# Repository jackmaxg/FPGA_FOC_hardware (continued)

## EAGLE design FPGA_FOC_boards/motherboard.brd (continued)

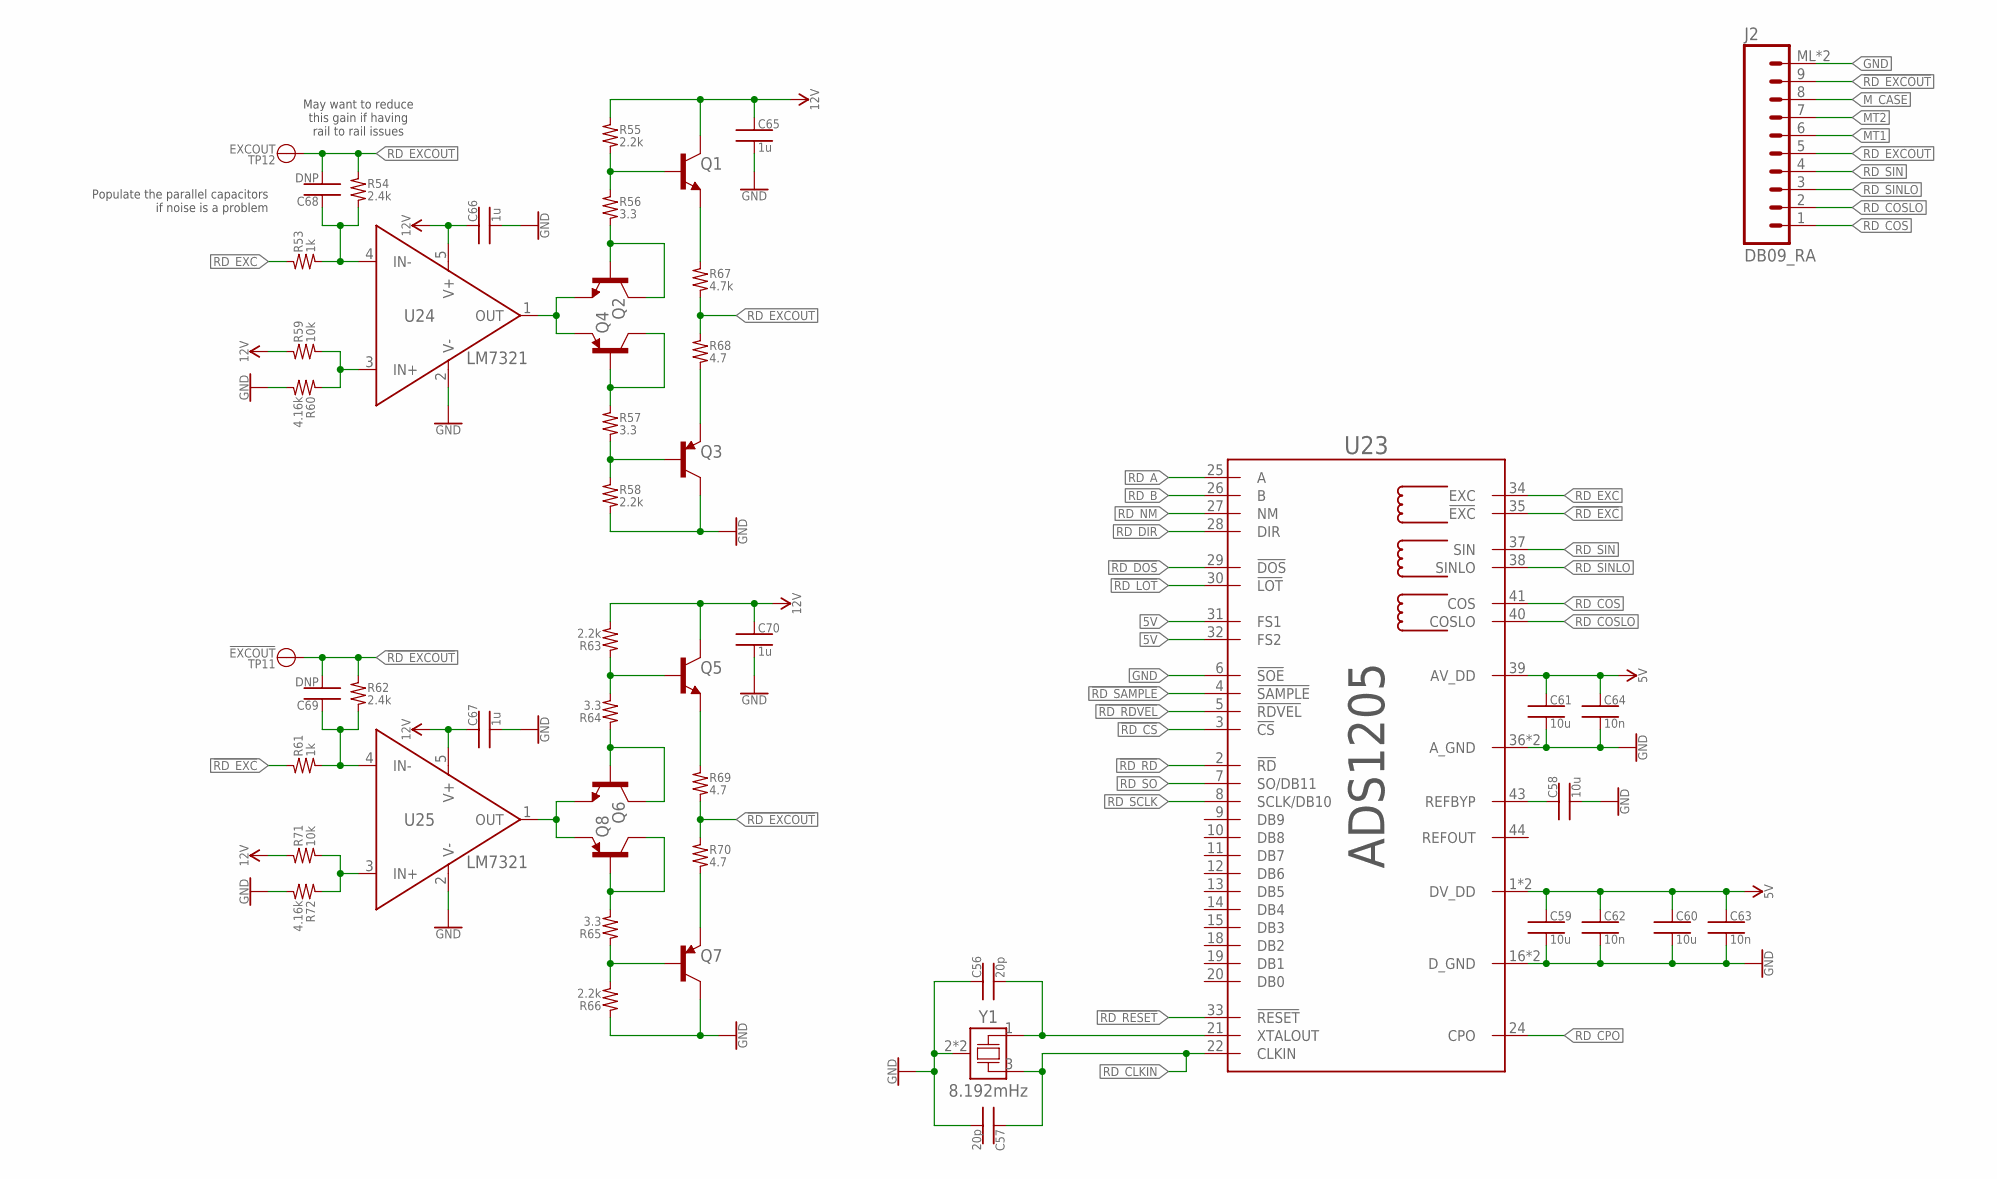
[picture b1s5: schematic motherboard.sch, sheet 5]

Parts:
C56, C57: 20p; 0402
C58, C59, C60, C61: 10u; 0603
C62, C63, C64: 10n; 0402
C65, C66, C67, C70: 1u; 0402
C68, C69: DNP; 0402
J2: DB09_RA; AE10921
Q1, Q2, Q5, Q6: BJT_NPN; SOT23-3
Q3, Q4, Q7, Q8: BJT_PNP; SOT23-3
R53, R61: 1k; 0402
R54, R62: 2.4k; 0402
R55, R58, R63, R66: 2.2k; 0402
R56, R57, R64, R65: 3.3; 0402
R59, R71: 10k; 0402
R60, R72: 4.16k; 0402
R67: 4.7k; 0805
R68, R69, R70: 4.7; 0805
TP11: !EXCOUT; 1X01_50MIL
TP12: EXCOUT; 1X01_50MIL
U23: ADS1205; LQFP44
U24, U25: LM7321; SOT23-5
Y1: 8.192mHz; 5X3.2MM_SMD_XTAL

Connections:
5V: C59.1, C60.1, C61.1, C62.1, C63.1, C64.1, U23.1 (DV_DD), U23.17 (DV_DD), U23.31 (FS1), U23.32 (FS2), U23.39 (AV_DD); also elsewhere on the board
12V: C65.1, C66.1, C67.1, C70.1, Q1.3 (C), Q5.3 (C), R55.1, R59.1, R63.2, R71.1, U24.5 (V+), U25.5 (V+); also elsewhere on the board
!RD_CS: U23.3 (!CS); also elsewhere on the board
!RD_DOS: U23.29 (!DOS); also elsewhere on the board
!RD_EXC: R61.1, U23.35 (!EXC)
!RD_EXCOUT: C69.2, J2.9, R62.1, R69.2, R70.1, TP11.1
!RD_LOT: U23.30 (!LOT); also elsewhere on the board
!RD_RD: U23.2 (!RD); also elsewhere on the board
!RD_RDVEL: U23.5 (!RDVEL); also elsewhere on the board
!RD_RESET: U23.33 (!RESET); also elsewhere on the board
!RD_SAMPLE: U23.4 (!SAMPLE); also elsewhere on the board
GND: C56.1, C57.2, C58.2, C59.2, C60.2, C61.2, C62.2, C63.2, C64.2, C65.2, C66.2, C67.2, C70.2, J2.ML (10), J2.MR (10), Q3.3 (C), Q7.3 (C), R58.2, R60.2, R66.1, R72.2, U23.6 (!SOE), U23.16 (D_GND), U23.23 (D_GND), U23.36 (A_GND), U23.42 (A_GND), U24.2 (V-), U25.2 (V-), Y1.2 (CASE), Y1.4 (CASE); also elsewhere on the board
MT1: J2.6
MT2: J2.7
M_CASE: J2.8
Q1_BASE: Q1.1 (B), R55.2, R56.1
Q1_EMITTER: Q1.2 (E), R67.1
Q2_BC: Q2.1 (B), Q2.3 (C), R56.2
Q3_BASE: Q3.1 (B), R57.2, R58.1
Q3_EMITTER: Q3.2 (E), R68.2
Q4_BC: Q4.1 (B), Q4.3 (C), R57.1
Q5_BASE: Q5.1 (B), R63.1, R64.2
Q5_EMITTER: Q5.2 (E), R69.1
Q6_BC: Q6.1 (B), Q6.3 (C), R64.1
Q7_BASE: Q7.1 (B), R65.1, R66.2
Q7_EMITTER: Q7.2 (E), R70.2
Q8_BC: Q8.1 (B), Q8.3 (C), R65.2
RD_A: U23.25 (A); also elsewhere on the board
RD_B: U23.26 (B); also elsewhere on the board
RD_CLKIN: C57.1, U23.22 (CLKIN), Y1.3 (X2)
RD_COS: J2.1, U23.41 (COS)
RD_COSLO: J2.2, U23.40 (COSLO)
RD_CPO: U23.24 (CPO)
RD_DIR: U23.28 (DIR); also elsewhere on the board
RD_EXC: R53.1, U23.34 (EXC)
RD_EXCOUT: C68.2, J2.5, R54.1, R67.2, R68.1, TP12.1
RD_NM: U23.27 (NM); also elsewhere on the board
RD_REFBYP: C58.1, U23.43 (REFBYP)
RD_SCLK: U23.8 (SCLK/DB10); also elsewhere on the board
RD_SIN: J2.4, U23.37 (SIN)
RD_SINLO: J2.3, U23.38 (SINLO)
RD_SO: U23.7 (SO/DB11); also elsewhere on the board
RD_XTALOUT: C56.2, U23.21 (XTALOUT), Y1.1 (X1)
U24_IN+: R59.2, R60.1, U24.3 (IN+)
U24_IN-: C68.1, R53.2, R54.2, U24.4 (IN-)
U24_OUT: Q2.2 (E), Q4.2 (E), U24.1 (OUT)
U25_IN+: R71.2, R72.1, U25.3 (IN+)
U25_IN-: C69.1, R61.2, R62.2, U25.4 (IN-)
U25_OUT: Q6.2 (E), Q8.2 (E), U25.1 (OUT)

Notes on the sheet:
Populate the parallel capacitors if noise is a problem
May want to reduce this gain if having rail to rail issues

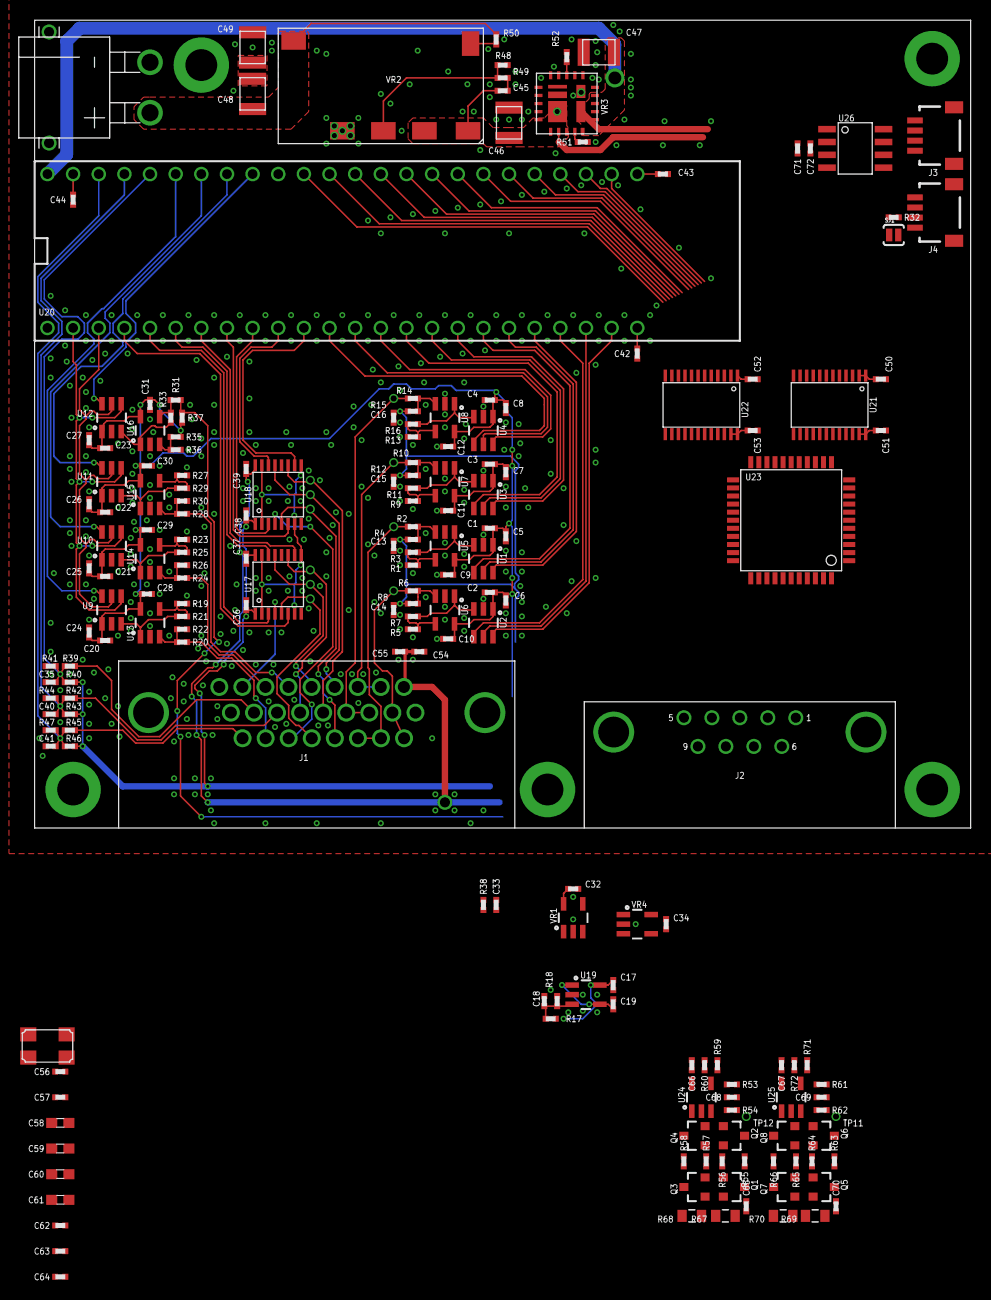
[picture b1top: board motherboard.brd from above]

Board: 2 copper layers, 92.7 x 80.0 mm, 205 parts (0 on the bottom side), 149 nets.

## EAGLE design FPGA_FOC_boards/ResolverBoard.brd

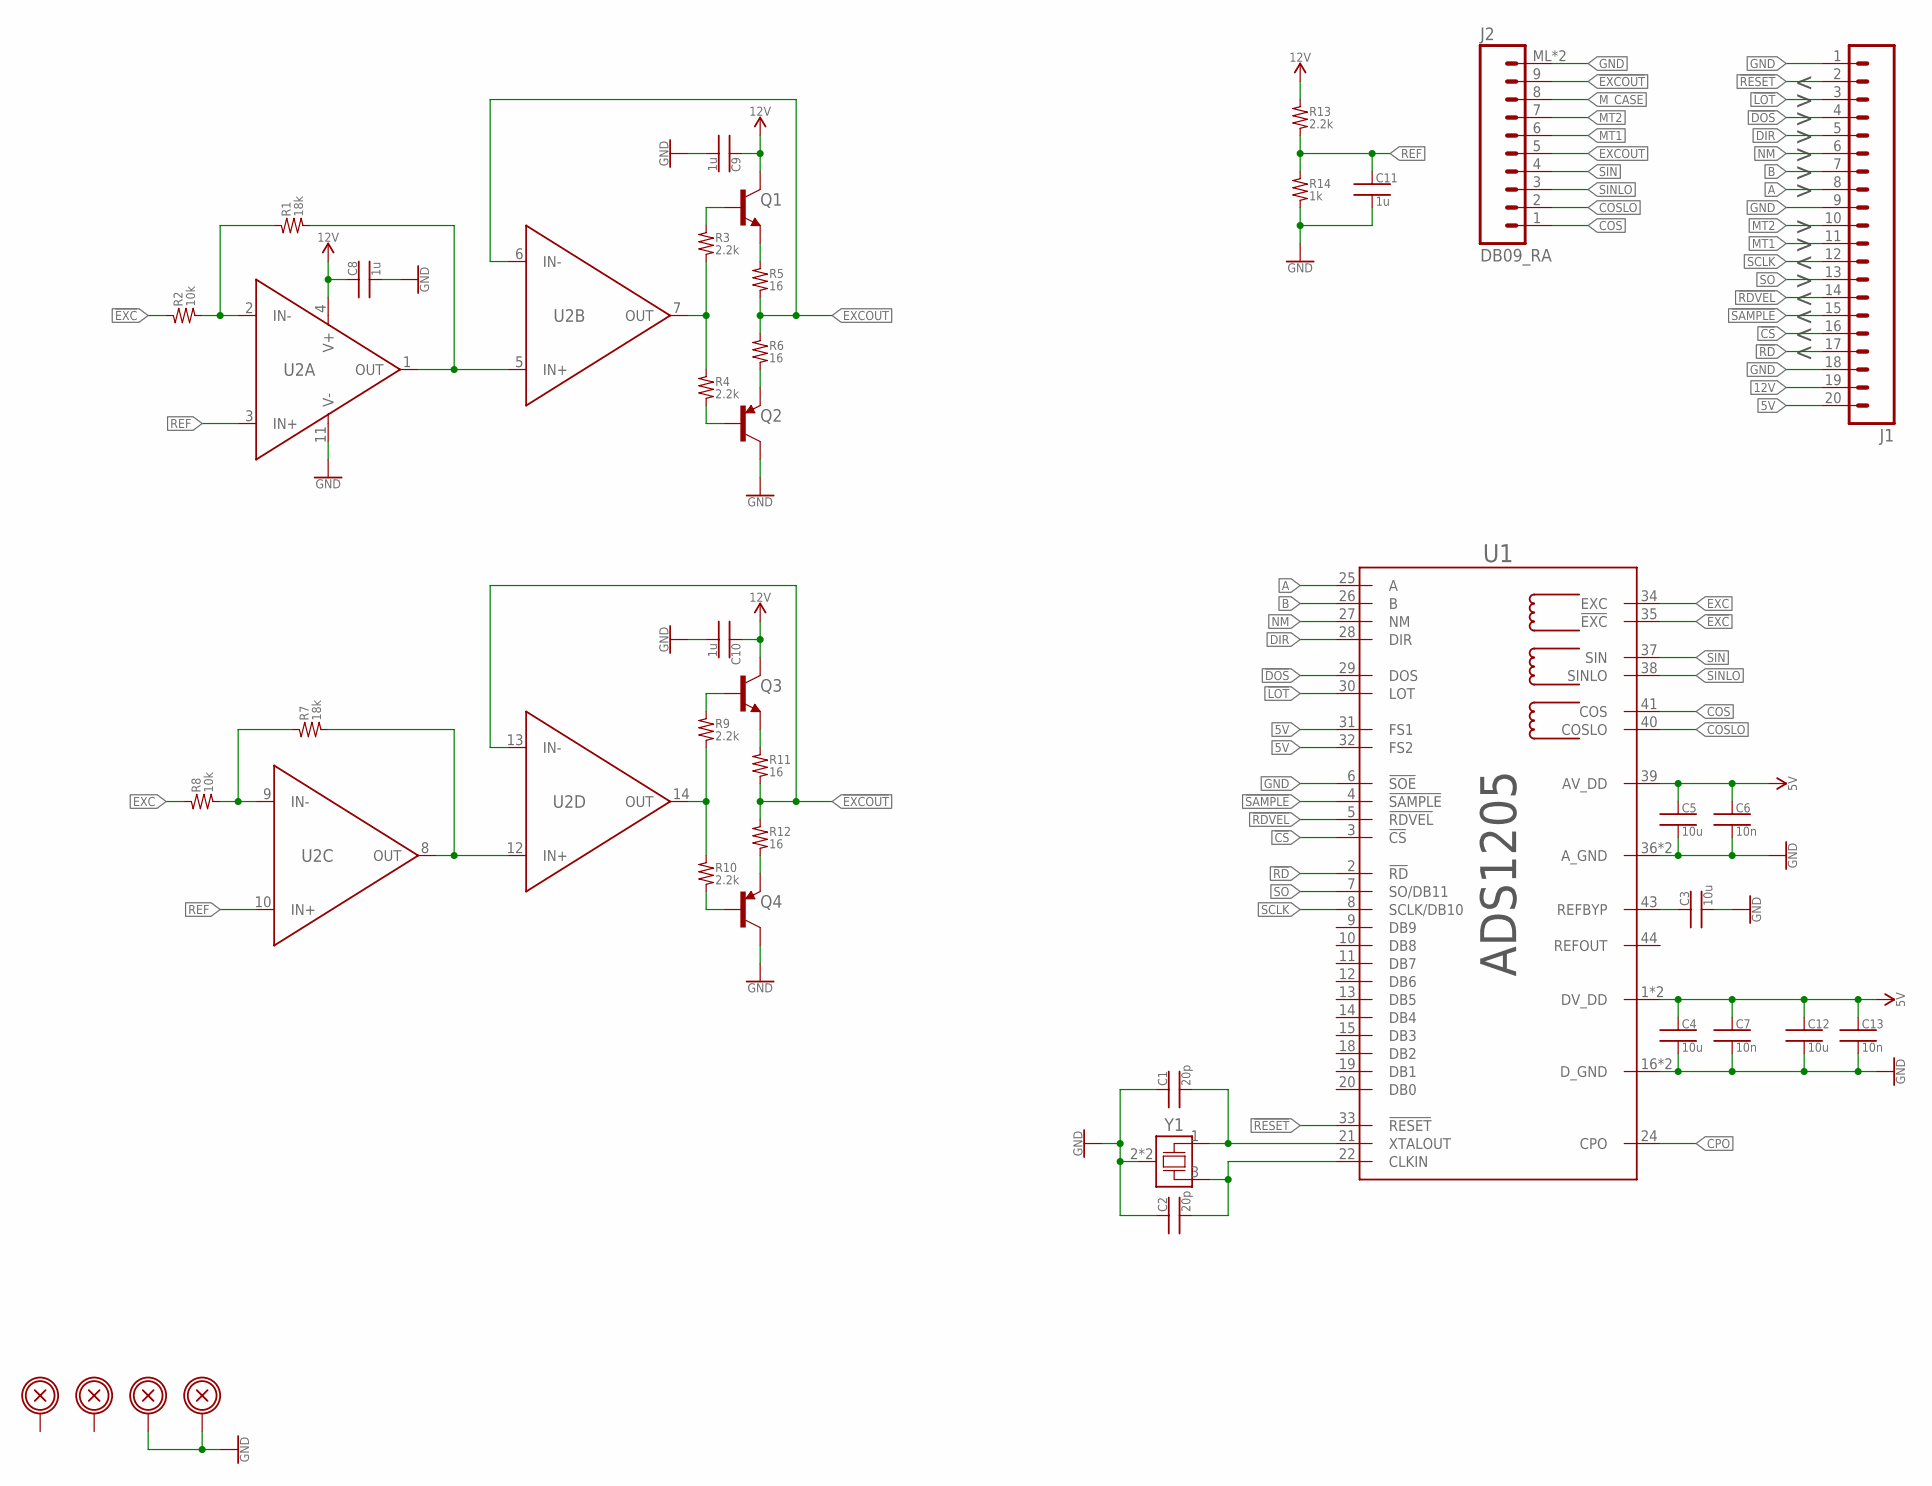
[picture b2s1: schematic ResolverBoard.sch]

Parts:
C1, C2: 20p; 0402
C3, C4, C5, C12: 10u; 0603
C6, C7, C13: 10n; 0402
C8, C9, C10, C11: 1u; 0402
H1, H2, H3, H4: BOLTHOLE_M3; M3_HOLE
J1: M20; 1X20
J2: DB09_RA; AE10921
Q1, Q3: BJT_NPN; SOT23-3
Q2, Q4: BJT_PNP; SOT23-3
R1, R7: 18k; 0402
R2, R8: 10k; 0402
R3, R4, R9, R10, R13: 2.2k; 0402
R5, R6, R11, R12: 16; 0805
R14: 1k; 0402
U1: ADS1205; LQFP44
U2: OPA4171D; SOIC_14
Y1: LFXTAL061486; 5X3.2MM_SMD_XTAL

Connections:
5V: C4.1, C5.1, C6.1, C7.1, C12.1, C13.1, J1.20, U1.1 (DV_DD), U1.17 (DV_DD), U1.31 (FS1), U1.32 (FS2), U1.39 (AV_DD)
12V: C8.1, C9.1, C10.1, J1.19, Q1.3 (C), Q3.3 (C), R13.1, U2.4 (V+)
!CS: J1.16, U1.3 (!CS)
!DOS: J1.4, U1.29 (DOS)
!EXC: R2.1, U1.35 (!EXC)
!EXCOUT: J2.9, R11.2, R12.1, U2.13 (IN-)
!LOT: J1.3, U1.30 (LOT)
!RD: J1.17, U1.2 (!RD)
!RDVEL: J1.14, U1.5 (!RDVEL)
!RESET: J1.2, U1.33 (!RESET)
!SAMPLE: J1.15, U1.4 (!SAMPLE)
A: J1.8, U1.25 (A)
B: J1.7, U1.26 (B)
CLKIN: C2.2, U1.22 (CLKIN), Y1.3 (X2)
COS: J2.1, U1.41 (COS)
COSLO: J2.2, U1.40 (COSLO)
CPO: U1.24 (CPO)
DIR: J1.5, U1.28 (DIR)
EXC: R8.1, U1.34 (EXC)
EXCOUT: J2.5, R5.2, R6.1, U2.6 (IN-)
GND: C1.1, C2.1, C3.2, C4.2, C5.2, C6.2, C7.2, C8.2, C9.2, C10.2, C11.2, C12.2, C13.2, H3.P, H4.P, J1.1, J1.9, J1.18, J2.ML (10), J2.MR (10), Q2.3 (C), Q4.3 (C), R14.2, U1.6 (!SOE), U1.16 (D_GND), U1.23 (D_GND), U1.36 (A_GND), U1.42 (A_GND), U2.11 (V-), Y1.2 (CASE), Y1.4 (CASE)
MT1: J1.11, J2.6
MT2: J1.10, J2.7
M_CASE: J2.8
NM: J1.6, U1.27 (NM)
Q1BASE: Q1.1 (B), R3.1
Q1EMITTER: Q1.2 (E), R5.1
Q2BASE: Q2.1 (B), R4.2
Q2EMITTER: Q2.2 (E), R6.2
Q3BASE: Q3.1 (B), R9.1
Q3EMITTER: Q3.2 (E), R11.1
Q4BASE: Q4.1 (B), R10.2
Q4EMITTER: Q4.2 (E), R12.2
REF: C11.1, R13.2, R14.1, U2.3 (IN+), U2.10 (IN+)
REFBYP: C3.1, U1.43 (REFBYP)
SCLK: J1.12, U1.8 (SCLK/DB10)
SIN: J2.4, U1.37 (SIN)
SINLO: J2.3, U1.38 (SINLO)
SO: J1.13, U1.7 (SO/DB11)
U2A_IN-: R1.1, R2.2, U2.2 (IN-)
U2A_OUT: R1.2, U2.1 (OUT), U2.5 (IN+)
U2B_OUT: R3.2, R4.1, U2.7 (OUT)
U2C_IN-: R7.1, R8.2, U2.9 (IN-)
U2C_OUT: R7.2, U2.8 (OUT), U2.12 (IN+)
U2D_OUT: R9.2, R10.1, U2.14 (OUT)
XTALOUT: C1.2, U1.21 (XTALOUT), Y1.1 (X1)

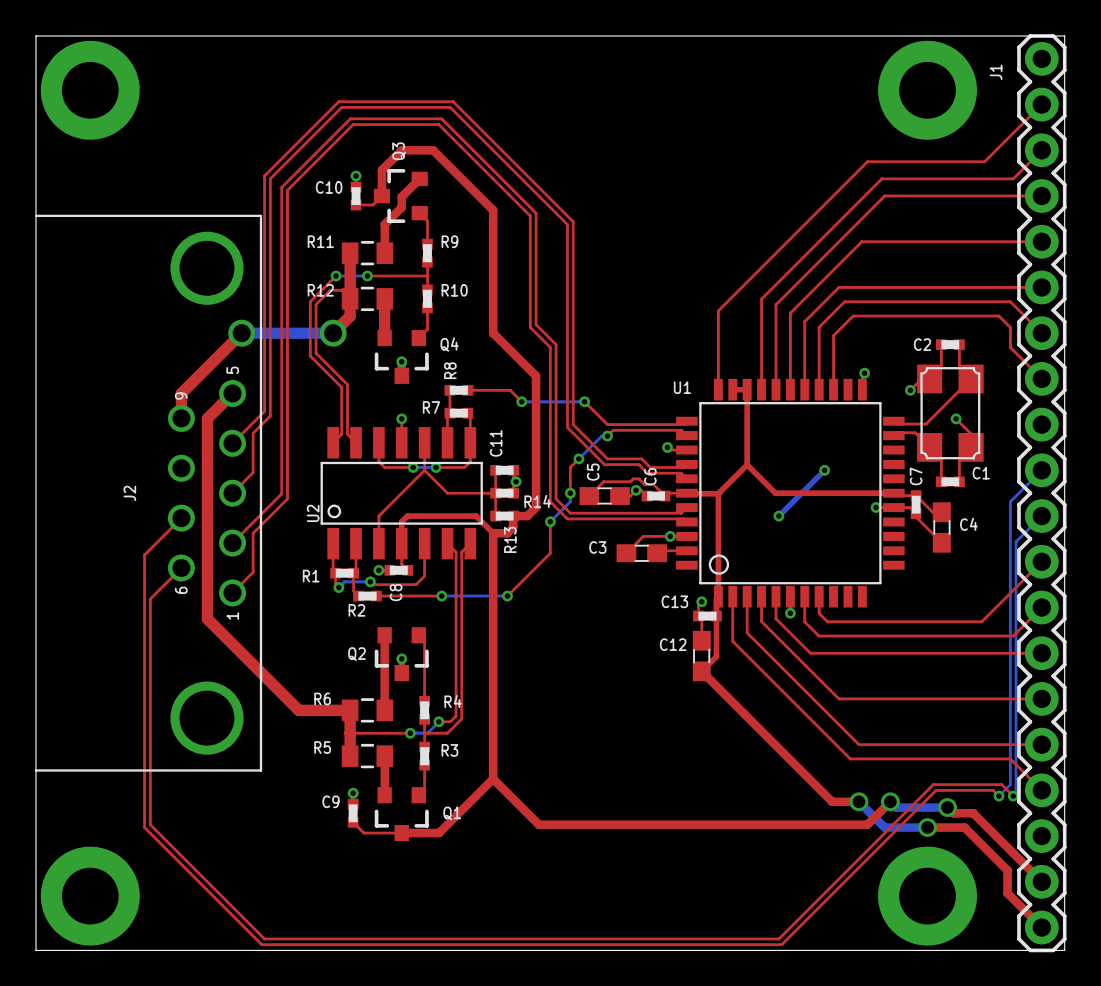
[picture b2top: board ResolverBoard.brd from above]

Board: 2 copper layers, 57.1 x 50.8 mm, 40 parts (0 on the bottom side), 44 nets.

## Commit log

2019-11-03 tweaked gitattributes, and started a simple eagleproject
2019-11-25 first revision of both motherboard and resolverboard finished
2020-01-09 added the V1 BOM, consider this the last V1 commit
2020-01-10 started adding in the resolver hardware onto the motherboard, began ripping up some parts of the v1 board to make room for resolver hardware
2020-01-12 did some calculations for part values for the resolver buffer stage
2020-01-12 updated the gitignore to ignore matlab .asv files
2020-01-12 started the CCU board
